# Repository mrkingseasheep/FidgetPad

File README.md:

# FidgetPad V2.1

Keyboards are flat. Flat is boring. Why not add some turny things?

This is a 3x3 macropad with 2 rotary encoders that originally had an OLED screen before I realized that I could trade it in for a 3x3 keyboard instead of a 1x3 row.
It's meant to supplement my normal shitty keyboard which lacks a volume knob, something that I sorely miss.
Btw the git commit history is so empty because I had some large .blend files in my last repo that I just couldn't get rid of (so GitHub didn't let me push) :P

## BOM

| Item             | QNT |
| ---------------- | --- |
| MX Style Switchs | 9   |
| Keycaps          | 9   |
| 1N4148 Diode     | 9   |
| EC11 Encoders    | 2   |
| XIAO RP2040      | 1   |
| M3 Screws        | 2   |
| M3 Heat Insert   | 2   |
| PCB              | 1   |
| Case             | 1   |

## Images

It took a comical amount of time for me to realize that my schematic could be neat. Don't look at V1. Also turns out I didn't need pullup resistors on every single pin. Neat!

There are breakout pins for GND, +5V and +3V3 but I'm not sure if I want to use them. I put them there just in case I wanted to add some jank LEDs at any point in the future.

My 3D models disappeared :<

The PCB attaches to the case with 2 M3 screws. The lid should hopefully work without any screws.

wow grayscale, how captivating.

Blender is hard.

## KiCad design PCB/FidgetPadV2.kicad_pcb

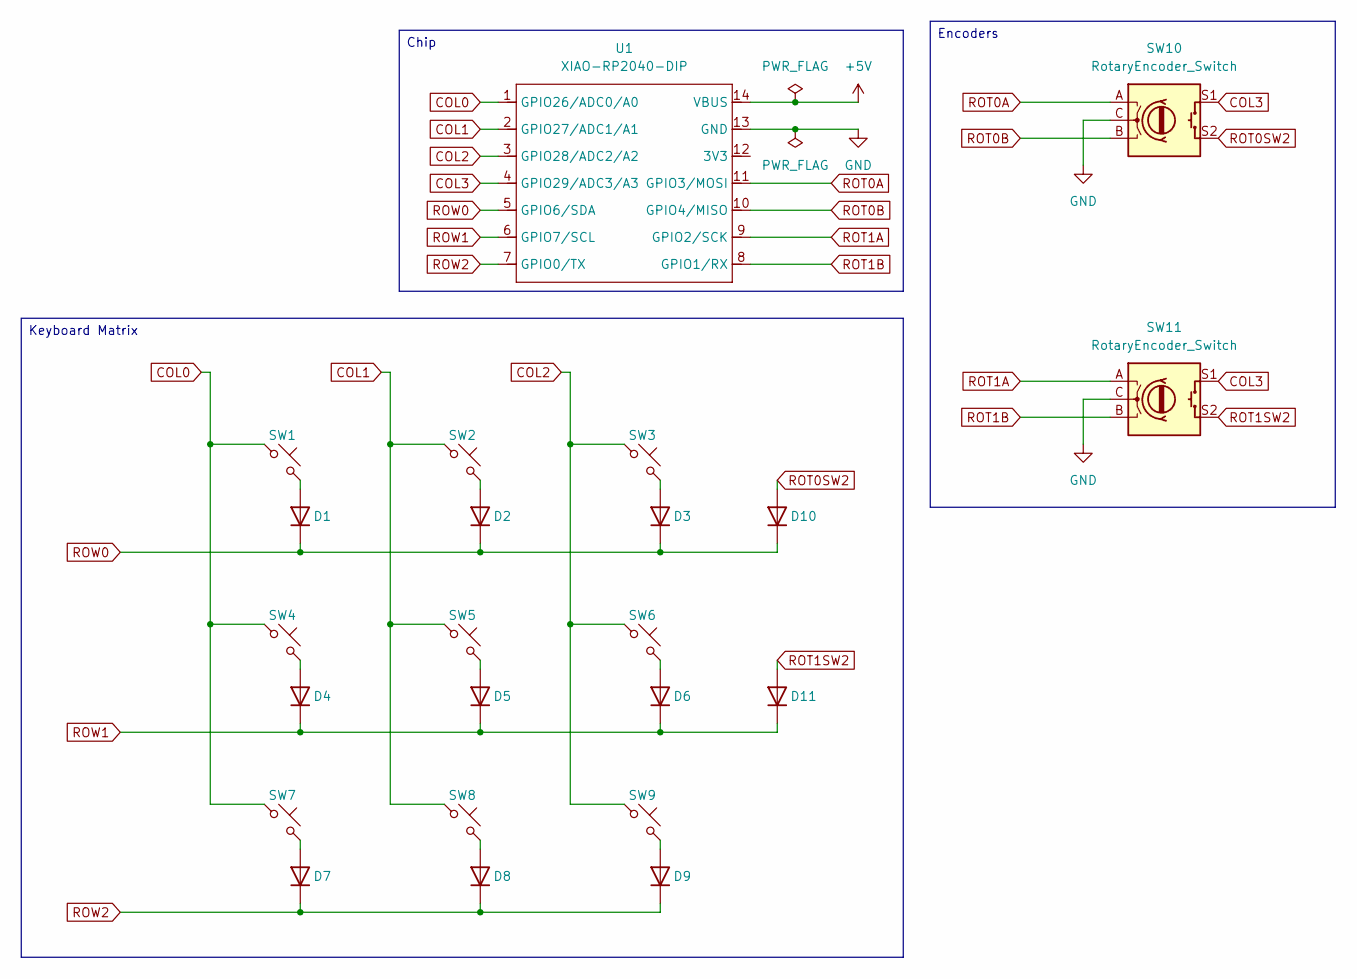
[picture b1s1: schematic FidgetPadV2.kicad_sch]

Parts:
D1, D2, D3, D4, D5, D6, D7, D8, D9, D10, D11: 1N4148; D_DO-35_SOD27_P7.62mm_Horizontal
SW1, SW2, SW3, SW4, SW5, SW6, SW7, SW8, SW9: SW_Push_45deg; SW_Cherry_MX_1.00u_PCB
SW10, SW11: RotaryEncoder_Switch; RotaryEncoder_Alps_EC11E-Switch_Vertical_H20mm
U1: XIAO-RP2040-DIP

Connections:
+5V: U1.14 (VBUS); also elsewhere on the board
COL0: SW1.1, SW4.1, SW7.1, U1.1 (GPIO26/ADC0/A0)
COL1: SW2.1, SW5.1, SW8.1, U1.2 (GPIO27/ADC1/A1)
COL2: SW3.1, SW6.1, SW9.1, U1.3 (GPIO28/ADC2/A2)
COL3: SW10.S1, SW11.S1, U1.4 (GPIO29/ADC3/A3)
GND: SW10.C, SW11.C, U1.13 (GND); also elsewhere on the board
unnamed: D1.2 (A), SW1.2
unnamed: D2.2 (A), SW2.2
unnamed: D3.2 (A), SW3.2
unnamed: D4.2 (A), SW4.2
unnamed: D5.2 (A), SW5.2
unnamed: D6.2 (A), SW6.2
unnamed: D7.2 (A), SW7.2
unnamed: D8.2 (A), SW8.2
unnamed: D9.2 (A), SW9.2
ROT0A: SW10.A, U1.11 (GPIO3/MOSI)
ROT0B: SW10.B, U1.10 (GPIO4/MISO)
ROT0SW2: D10.2 (A), SW10.S2
ROT1A: SW11.A, U1.9 (GPIO2/SCK)
ROT1B: SW11.B, U1.8 (GPIO1/RX)
ROT1SW2: D11.2 (A), SW11.S2
ROW0: D1.1 (K), D2.1 (K), D3.1 (K), D10.1 (K), U1.5 (GPIO6/SDA)
ROW1: D4.1 (K), D5.1 (K), D6.1 (K), D11.1 (K), U1.6 (GPIO7/SCL)
ROW2: D7.1 (K), D8.1 (K), D9.1 (K), U1.7 (GPIO0/TX)

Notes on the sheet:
Keyboard Matrix
Chip
Encoders

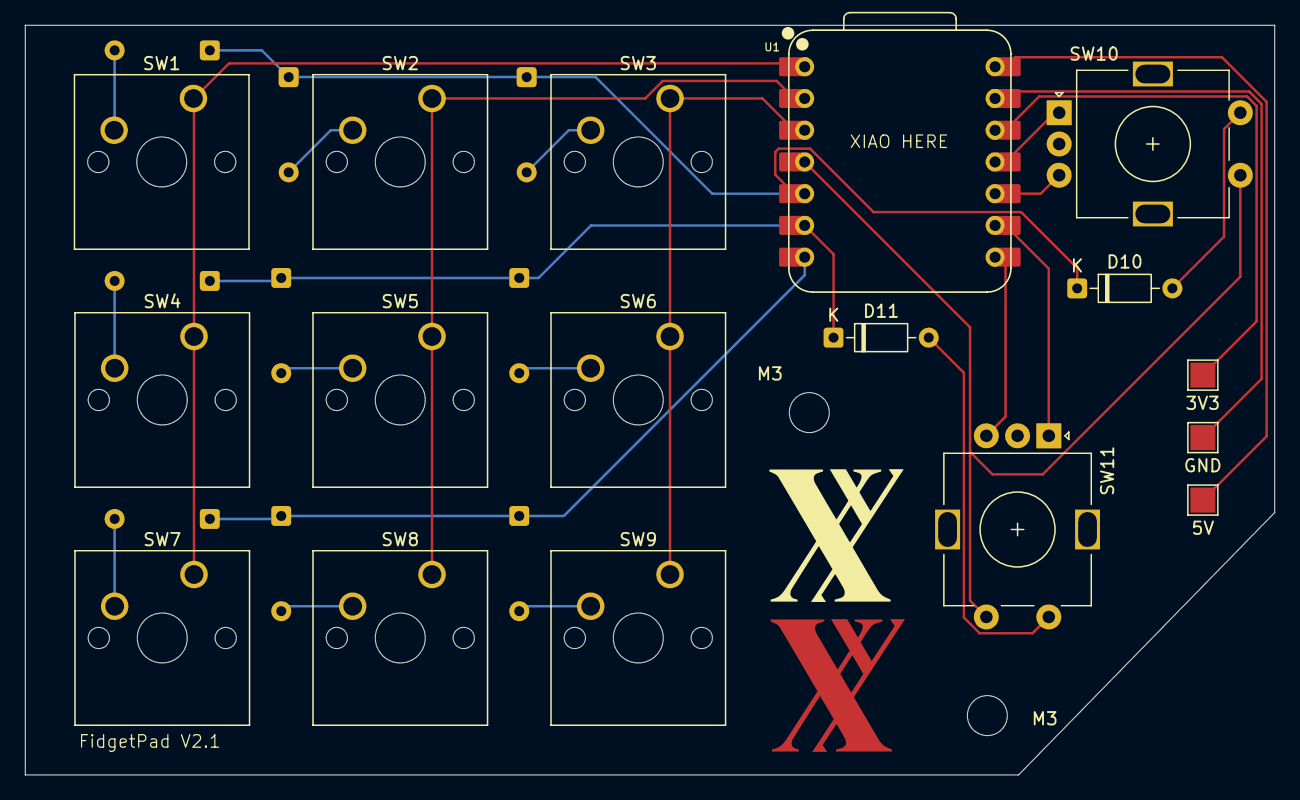
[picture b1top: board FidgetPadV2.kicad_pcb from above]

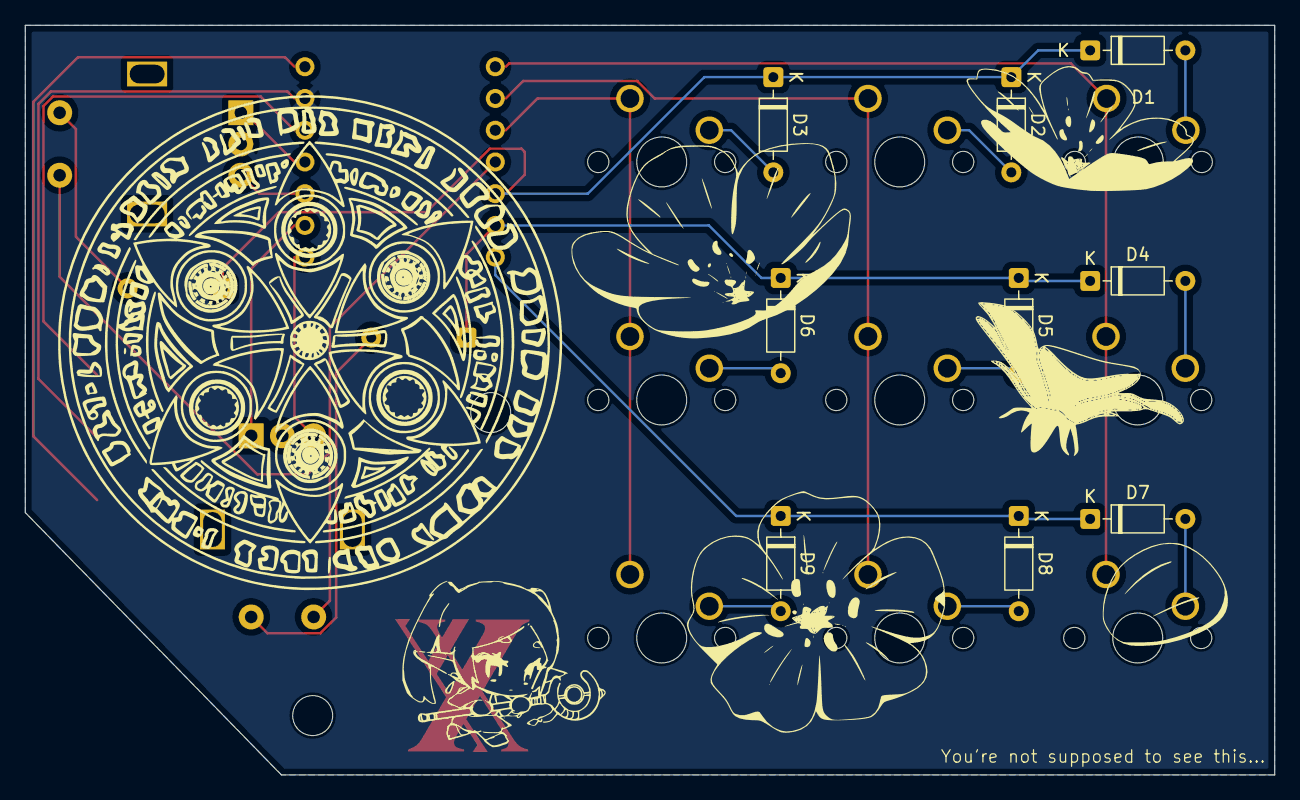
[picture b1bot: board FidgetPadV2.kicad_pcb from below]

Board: 2 copper layers, 100.0 x 60.0 mm, 28 parts (9 on the bottom side), 24 nets.

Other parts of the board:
3V3, 5V: TestPoint_Pad_2.0x2.0mm
GND: TestPoint_Pad_2.0x2.0mm
M3, M3#2: MountingHole_3.2mm_M3

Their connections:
+5V: 5V.1; also elsewhere on the board
GND: GND.1; also elsewhere on the board

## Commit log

2025-07-04 Old repo had large files, for submission
2025-07-04 Create LICENSE
2025-07-04 added images
2025-07-04 added snarky comments
2025-07-04 Updated exploded view
